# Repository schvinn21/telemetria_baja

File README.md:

# 📡 Projeto de Telemetria CAN com ESP32

Este projeto realiza a leitura de dados do acelerômetro MPU6050 e do módulo GPS NEO-M8N, transmitindo-os via protocolo CAN utilizando dois ESP32 e módulos com CI SN65HVD230. O objetivo é facilitar a coleta de dados em tempo real em ambientes como veículos off-road (ex: Baja SAE).

---

## 📁 Estrutura de Diretórios Recomendada

```bash
project-name/
├── CMakeLists.txt
├── sdkconfig
├── sdkconfig.defaults
├── main/
│   ├── main.c
│   └── CMakeLists.txt
├── components/
│   ├── mpu6050/
│   │   ├── mpu6050.c
│   │   ├── mpu6050.h
│   │   └── CMakeLists.txt
│   ├── gps/
│   │   ├── gps.c
│   │   ├── gps.h
│   │   └── CMakeLists.txt
│   └── can_transmiter/
│       ├── can_transmiter.c
│       ├── can_transmiter.h
│       └── CMakeLists.txt
├── .gitignore
└── README.md
```

> ❗ **Atenção:** A pasta `build/` gerada na compilação não deve ser versionada. Certifique-se de incluí-la no `.gitignore`.

---

## 💻 Requisitos para Execução

### 🧰 Instalações Necessárias

1. [ESP-IDF](https://docs.espressif.com/projects/esp-idf/en/latest/esp32/get-started/index.html)
2. Python 3 (recomendado usar virtualenv)
3. Dependências via pip:
   ```bash
   pip install esptool pyserial
   ```

### 📦 Drivers (Windows)

- Driver USB-to-Serial para ESP32 (CH340 ou CP2102)

---

## 🛠️ Como Compilar e Rodar

1. Configure o ambiente:
   ```bash
   . $HOME/esp/esp-idf/export.sh
   ```

2. Navegue até o diretório do projeto:
   ```bash
   cd project-name
   ```

3. Compile e carregue:
   ```bash
   idf.py build
   idf.py -p /dev/ttyUSB0 flash monitor
   ```

---

## 🚐 Funcionamento da Comunicação CAN

A rede CAN (Controller Area Network) é utilizada para comunicação entre microcontroladores, permitindo troca de dados em tempo real, com alta confiabilidade e resistência a ruído.

### ✅ Características:

- Comunicação serial diferencial (alta imunidade a interferências)
- Taxa usada: **500 kbps**
- Até **8 bytes por frame CAN**
- Prioridade de mensagens baseada no ID (menor ID = maior prioridade)

### 🔧 Aplicação neste Projeto:

Dois ESP32 comunicam-se via CAN:

- O **Transmissor** envia dados do MPU6050 e GPS usando dois frames:
  - `ID 0x123`: Aceleração X, Y, Z
  - `ID 0x124`: Latitude e Longitude (tipo `float`, codificados em IEEE 754)

- O **Receptor** decodifica os frames recebidos e imprime os valores no terminal.

> ⚠️ Os módulos CAN (SN65HVD230) devem ser ligados com resistores de terminação de 120 Ω entre CAN_H e CAN_L.

---

## 📌 Observações

- O GPS deve estar em ambiente aberto para obter sinal.
- Certifique-se de alimentar corretamente os módulos. O GPS e o CAN podem exigir corrente acima de 100 mA.
- Evite subir arquivos como `build/` e `.pioenvs/` ao repositório. Use `.gitignore` corretamente.

---

## 📷 Exemplo de Saída

```
Accel X: -520, Y: 256, Z: 16234
Latitude: -30.0457
Longitude: -51.2309
```

---

## 📍 Próximos Passos

- Envio dos dados via rede GSM (SIM900A)
- Visualização em dashboard web
- Armazenamento local (SD Card) ou remoto (MQTT, REST API)

---

Desenvolvido por **Eduardo Schvinn**  
Projeto para aplicação em competições **Baja SAE** 🏁

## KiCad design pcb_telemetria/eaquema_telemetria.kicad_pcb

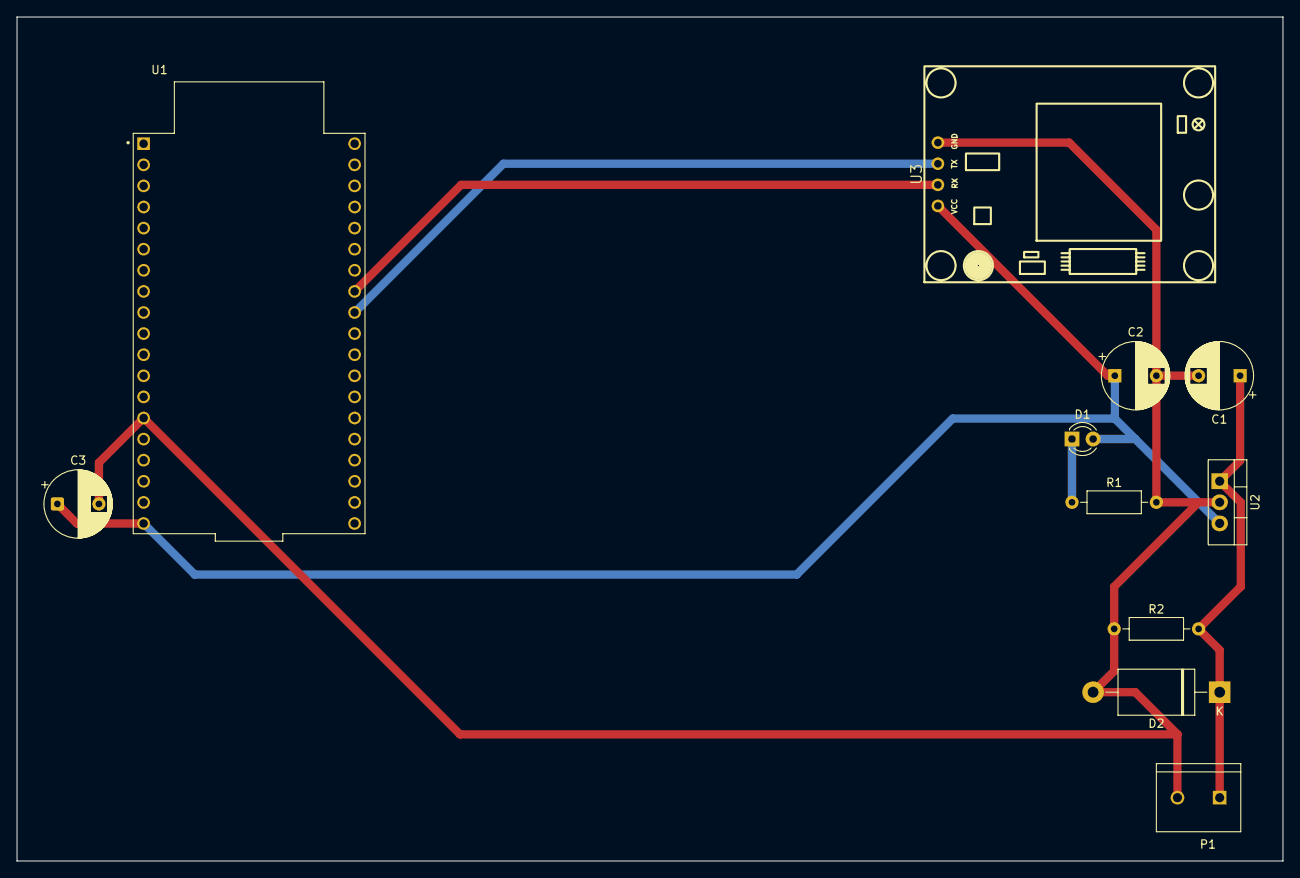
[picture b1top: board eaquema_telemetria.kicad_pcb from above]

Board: 2 copper layers, 152.4 x 101.6 mm, 11 parts (0 on the bottom side), 6 nets.

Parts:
C1: 220uF; CP_Radial_D8.0mm_P5.00mm
C2, C3: 10nF; CP_Radial_D8.0mm_P5.00mm
D1: LED; LED_D3.0mm
D2: 1N4742; D_DO-201AE_P15.24mm_Horizontal
P1: kre; TE_282837-2
R1: 220; R_Axial_DIN0207_L6.3mm_D2.5mm_P10.16mm_Horizontal
R2: 2.2; R_Axial_DIN0207_L6.3mm_D2.5mm_P10.16mm_Horizontal
U1: ESP32-DEVKITC; MODULE_ESP32-DEVKITC
U2: LM7805_TO220; TO-220-3_Vertical
U3: NEO6MV2; NEO-6M-V2-GPSMODULE-FOOTPRINT

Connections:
+5V: C2.1, C3.1, D1.2 (A), U1.19 (EXT_5V), U2.3 (VO), U3.1 (VCC)
+12V: C1.1, D2.1 (A1), P1.1, R2.2, U2.1 (VI)
GND: C1.2, C2.2, C3.2, D2.2 (A2), P1.2, R1.2, R2.1, U1.14 (GND1), U2.2 (GND), U3.4 (GND)
unnamed: D1.1 (K), R1.1
RX: U1.31 (IO19), U3.2 (RX)
TX: U1.30 (IO18), U3.3 (TX)

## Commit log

2025-03-06 README.md
2025-03-06 Create display
    Teste do display que o Leo fez.
2025-03-07 Add files via upload
    Documento com os componentes e as pinagens de cada PCB
2025-04-22 can_transmiter
    Código no qual faz a coleta dos dados de sensores e envia através da CAN.
2025-04-22 can_receiver
    Aqui é onde recebe os dados da CAN, e envia os dados para um servidor para exibição.
2025-08-09 Arquivos KICAD da pcb
2025-10-15 Adição do sensor de temperatura
2025-11-16 código completo
